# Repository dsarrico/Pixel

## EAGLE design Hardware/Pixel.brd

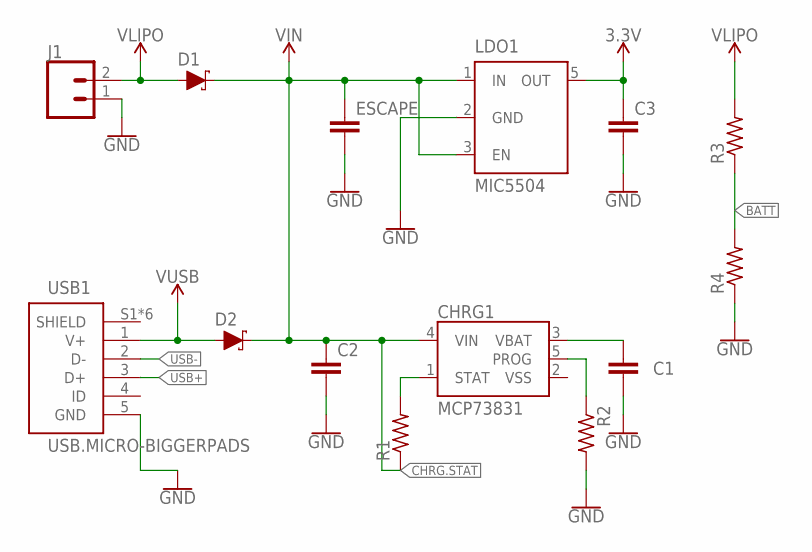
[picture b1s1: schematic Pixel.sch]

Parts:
C1, C2, C3: CAPACITOR0603; C0603
CHRG1: MCP73831; SOT23-5
D1, D2: SCHOTTKY-USC; USC
ESCAPE: CAPACITOR0603; C0603
J1: CONN_02; 1X02
LDO1: MIC5504; SOT23-5
R1, R2, R3, R4: RESISTOR0603; R0603
USB1: USB.MICRO-BIGGERPADS; USB-MICRO-01.BIGGERPADS

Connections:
3.3V: C3.1, LDO1.5 (OUT)
BATT: R3.1, R4.2
CHRG.STAT: C2.1, CHRG1.4 (VIN), D1.- (C), D2.- (C), ESCAPE.1, LDO1.1 (IN), LDO1.3 (EN), R1.1
GND: C1.2, C2.2, C3.2, ESCAPE.2, J1.1, LDO1.2 (GND), R2.2, R4.1, USB1.5 (GND)
unnamed: CHRG1.1 (STAT), R1.2
unnamed: CHRG1.5 (PROG), R2.1
unnamed: C1.1, CHRG1.3 (VBAT)
USB+: USB1.3 (D+)
USB-: USB1.2 (D-)
VLIPO: D1.+ (A), J1.2, R3.2
VSS: CHRG1.2 (VSS)
V_USB: D2.+ (A), USB1.1 (V+)

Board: 2 copper layers, 14 parts (0 on the bottom side), 9 nets, no tracks yet.
